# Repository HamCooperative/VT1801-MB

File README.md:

# VT1801-MB

宝峰 DM-1801 电台用 CH1801 充电座快充替换主板。

Replacement motherboard for Baofeng CH1801 charger for DM-1801 radio.

## 摘要 Introduction

由于使用不慎误将极性相反的宝峰 UV-5R 放上宝峰 DM-1801 充电座，我烧坏了两个
CH1801。这块板子在设计上避免了轻易被反接电池烧毁的问题，同时支持 2A 快速充电。

I killed two Baofeng CH1801 charging stations for DM-1801 by placing a UV-5R on
it, which has a battery contact polarity. This board comes with protection
against polarity reversal, and it also supports 2A fast charging.

## 开发工具 Development Tools

本项目使用 [KiCad][KiCad] 开发。请[下载][KiCadDownload]安装后再打开。

This project is developed using [KiCad][KiCad]. Please [download][KiCadDownload]
and install it before opening this project.

[KiCad]: https://kicad.org/
[KiCadDownload]: https://kicad.org/download/

## 版权 Copyright

版权所有 &copy; 2021 陈北宗。保留所有权利。

Copyright &copy; 2021 Max Chan. All rights reserved.

本作品是[三条款伯克利发行版协议][License]约束下的开源硬件。

This is Open Source Hardware under [3-clause BSD license][License].

[License]: LICENSE.md

### 特别禁止条款 Special Prohibitions

本作品及其派生作品禁止持有以下业余无线电呼号的人接触：

Holders of the following amateur radio call signs are prohibited from this work
and its derivatives:

* `BD4TWJ`
* `BG4FRZ`
* `BH4EXR`
* `BH4FEF`

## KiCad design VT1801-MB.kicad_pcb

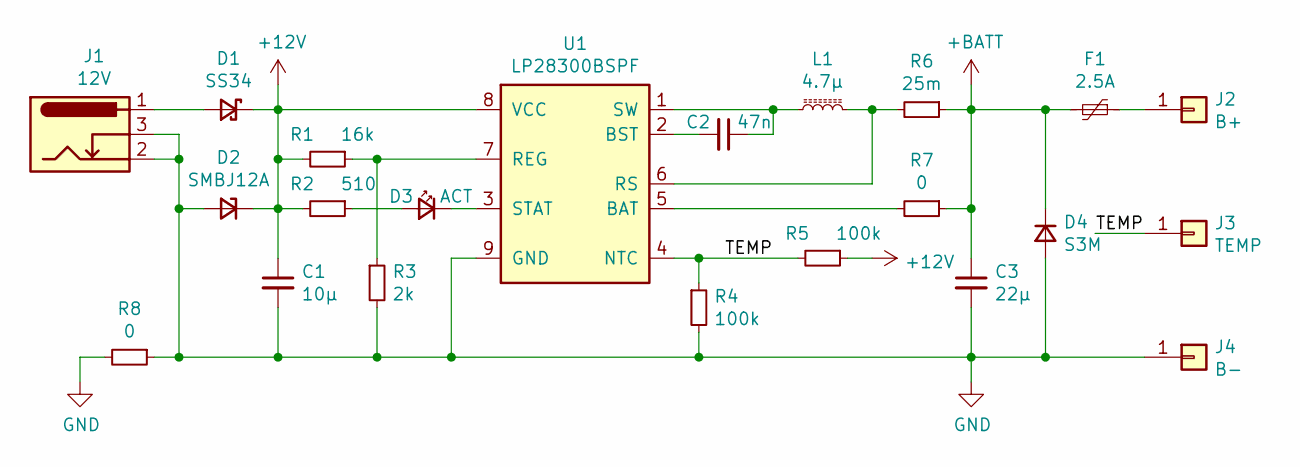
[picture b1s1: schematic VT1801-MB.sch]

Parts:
C1: 10µ; C_1206_3216Metric_Pad1.33x1.80mm_HandSolder
C2: 47n; C_0603_1608Metric_Pad1.08x0.95mm_HandSolder
C3: 22µ; C_1206_3216Metric_Pad1.33x1.80mm_HandSolder
D1: SS34; D_SMB
D2: SMBJ12A; D_SMB
D3: ACT; LED_D3.0mm_Horizontal_O1.27mm_Z2.0mm_Clear
D4: S3M; D_SMC
F1: 2.5A; L_1812_4532Metric_Pad1.30x3.40mm_HandSolder
J1: 12V; BarrelJack_Wuerth_6941xx301002
J2: B+; Pin_D1x2.5mm
J3: TEMP; Pin_D1x2.5mm
J4: B-; Pin_D1x2.5mm
L1: 4.7µ; L_Taiyo-Yuden_NR-60xx_HandSoldering
R1: 16k; R_0603_1608Metric_Pad0.98x0.95mm_HandSolder
R2: 510; R_0603_1608Metric_Pad0.98x0.95mm_HandSolder
R3: 2k; R_0603_1608Metric_Pad0.98x0.95mm_HandSolder
R4, R5: 100k; R_0603_1608Metric_Pad0.98x0.95mm_HandSolder
R6: 25m; R_2512_6332Metric_Pad1.40x3.35mm_HandSolder
R7: 0; R_0603_1608Metric_Pad0.98x0.95mm_HandSolder
R8: 0; R_0805_2012Metric_Pad1.20x1.40mm_HandSolder
U1: LP28300BSPF; SOIC-8-1EP_3.9x4.9mm_P1.27mm_EP2.41x3.3mm

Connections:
+12V: C1.1, D1.1 (K), D2.1 (K), R1.2, R2.2, R5.1, U1.8 (VCC)
+BATT: C3.1, D4.1 (K), F1.2, R6.1, R7.1
/TEMP: J3.1, R4.1, R5.2, U1.4 (NTC)
GND: C1.2, C3.2, D2.2 (A), D4.2 (A), J1.2, J1.3, J4.1, R3.2, R4.2, R8.1, R8.2, U1.9 (GND)
unnamed: C2.1, L1.2, U1.1 (SW)
unnamed: C2.2, U1.2 (BST)
unnamed: D1.2 (A), J1.1
unnamed: D3.1 (K), U1.3 (STAT)
unnamed: D3.2 (A), R2.1
unnamed: F1.1, J2.1
unnamed: L1.1, R6.2, U1.6 (RS)
unnamed: R1.1, R3.1, U1.7 (REG)
unnamed: R7.2, U1.5 (BAT)

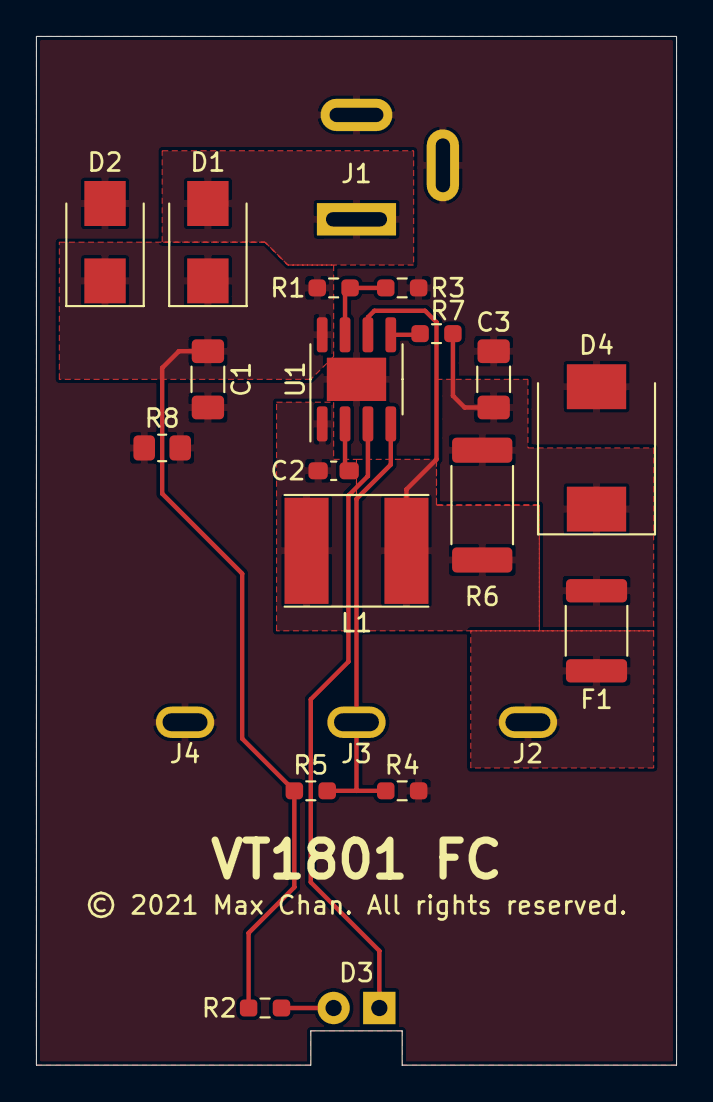
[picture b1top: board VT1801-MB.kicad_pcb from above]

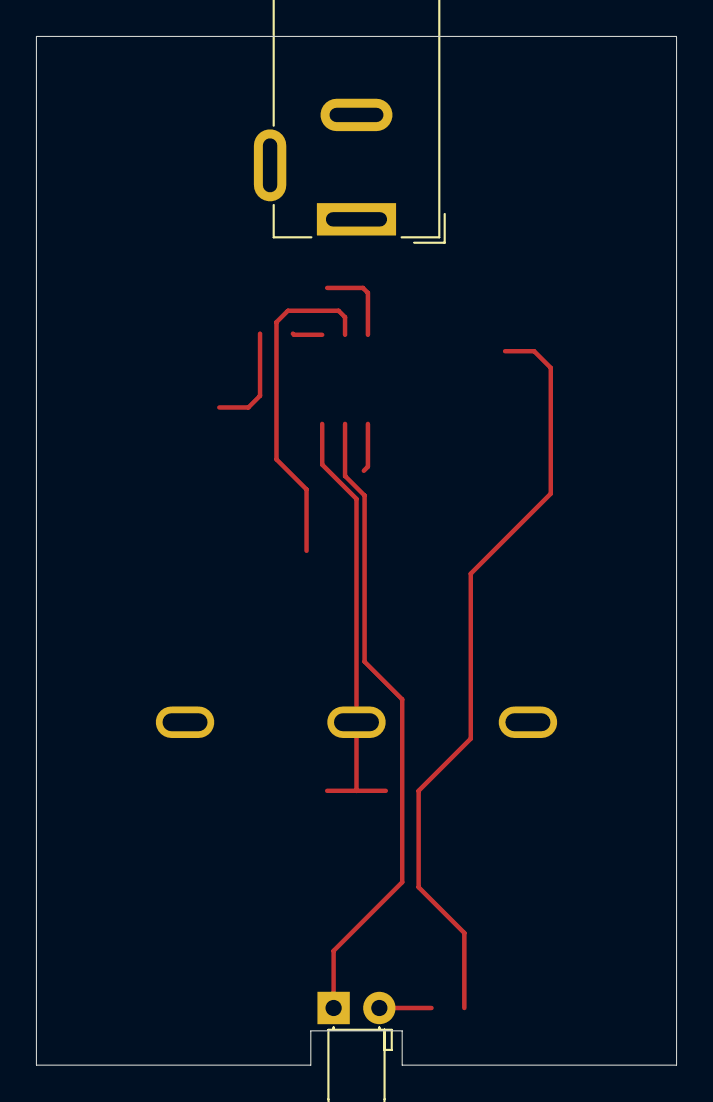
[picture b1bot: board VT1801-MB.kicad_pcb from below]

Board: 2 copper layers, 35.6 x 57.1 mm, 22 parts (2 on the bottom side), 13 nets.

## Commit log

2021-02-02 Code dump: finished project.
2021-02-02 Update ignore file to skip gerber files.
